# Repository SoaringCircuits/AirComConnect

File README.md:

# AirComConnect

## General remarks
This small board is designed to simplify and organize the wiring in your glider.
It provides a clean extension point to wire the cables for the AirAvionics AirCom.

## Electrical installation
Installation is easy, but some basic skills in creating cable harnesses are needed to create the connection from AirCom to the board.
The following diagram shows the harness to build to connect S100 and board. 

The board provides terminals for power and common inputs for a double seated glider with dynamic microphones and a speaker.

## D-SUB Connectors
The board uses one D-SUB High Density connector.
I recommend to use connectors with crimped contacts, but solderd ones will work as well.
All connections are direct lines, there is no need to crimp/solder more than one cable to a single contact.

## Wago Terminals
All terminals are easy to operate, just push the actuator with a little screwdriver and push-in or pull-out the conductor.

The terminals for fuses and devices are suitable for various types of wires:
- Solid concductor 0.2 - 1.5 mm^2
- Fine-stranded conductor 0.2 - 1.5 mm^2
- Fine-stranded conductor with ferrule 0.25 - 1.0 mm^2

The terminal for the main supply can handle conductors up to:
- Solid concductor 0.1 - 4.0 mm^2
- Fine-stranded conductor 0.1 - 4.0 mm^2
- Fine-stranded conductor with ferrule 0.25 - 2.5 mm^2

## Mechanical installation
The half housing is 3D-printed and reliably protects against short circuits on the contacts on the underside of the board.
With four mounting holes for M3 screws, the board can be securely and firmly mounted in the aircraft, with the screws fixing both the housing and the board at the same time.

## Disclaimer
Installation and use of the board are the sole responsibility of the user.
AirAvionics, the manufacturer of the AirCom, is and was NOT involved in the development of the board and can not be hold responsibly for any failures or damage to the device.
The board has been built to the best of my knowledge and belief, but no warranty or guarantee can be given for correct functioning or interference immunity.
The legal usability must be checked before each individual installation and, in case of doubt, clarified with competent and authorized personnel (CFS).

## Licence
Copyright Fabian Schöttler 2025.

This source describes Open Hardware and is licensed under the CERN-OHL-P
v2 or later.

You may redistribute and modify this documentation and make products
using it under the terms of the CERN-OHL-P v2 or later (https:/cern.ch/cern-ohl).
This documentation is distributed WITHOUT ANY EXPRESS OR IMPLIED
WARRANTY, INCLUDING OF MERCHANTABILITY, SATISFACTORY QUALITY
AND FITNESS FOR A PARTICULAR PURPOSE.
Please see the CERN-OHL-P v2 for applicable conditions

## Contact
If you have any questions or suggestions about the board, please send an e-mail to fabian@schoettlerhome.de.

------
Electrical, PCB and case design by [ScotteC](https://github.com/ScotteC)

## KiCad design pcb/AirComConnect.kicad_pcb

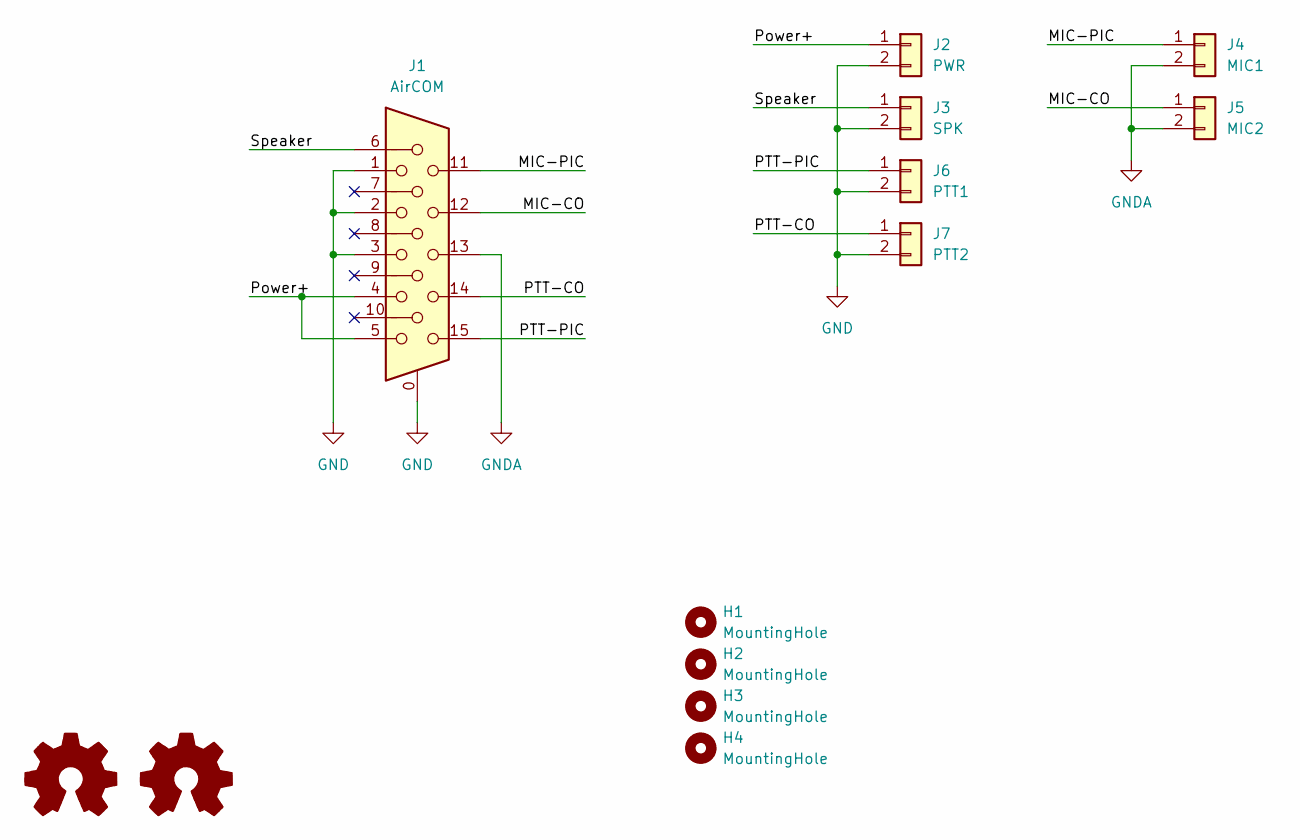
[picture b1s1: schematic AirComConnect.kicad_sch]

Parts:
H1, H2, H3, H4: MountingHole; MountingHole_3.2mm_M3
J1: AirCOM; DSUB-15-HD_Socket_Vertical_P2.29x1.98mm_MountingHoles
J2: PWR; Wago-250-202
J3: SPK; Wago-250-202
J4: MIC1; Wago-250-202
J5: MIC2; Wago-250-202
J6: PTT1; Wago-250-202
J7: PTT2; Wago-250-202

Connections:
/MIC-CO: J1.12, J5.1
/MIC-PIC: J1.11, J4.1
/PTT-CO: J1.14, J7.1
/PTT-PIC: J1.15, J6.1
/Power+: J1.4, J1.5, J2.1
/Speaker: J1.6, J3.1
GND: J1.0, J1.1, J1.2, J1.3, J2.2, J3.2, J6.2, J7.2
GNDA: J1.13, J4.2, J5.2

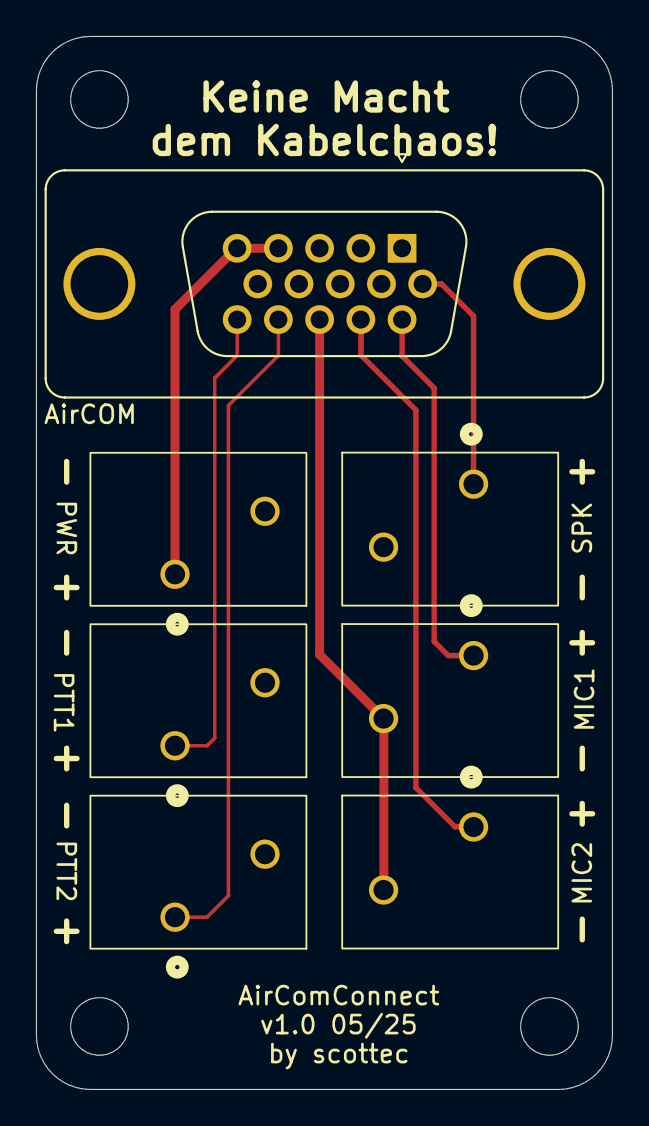
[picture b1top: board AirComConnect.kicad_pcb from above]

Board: 2 copper layers, 32.0 x 58.5 mm, 11 parts (0 on the bottom side), 8 nets.
